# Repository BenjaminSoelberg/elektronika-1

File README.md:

# ELEKTRONIKA-1 - A replacement module for a USSR made vintage LED watch anno 1978

## It actually works
The watch works very well and I am very happy with it.

It has been my daily driver for a few months by now with no problems what so ever.

It can show time, date and year which was more or less what you got in the original.

The module is based around:
* Texas Instruments MSP430fr2433 micro controller
* Austria Micro Systems AS1115 64 bit LED driver
* Vintage Hewlett Packard HP-5082-7414 4x7 segments + dot display
* CR2032 battery

## Source code
Modules:

* buttons.c - This is the button driver and it handles button events 
* clocksystem.c - Initializes the clock system in the MSP430
* config.h - Global timing and clock constants
* debounce.c - The button debounce detection and filtering using a sliding bit buffer
* display.c - Display update functions like content and intensity.
* driverlib_ng.c - My overloading of the TI MSP430 driver lib for better pin handling
* elektronika.c - Handles the control flow of everything
* render.c - Simple 7 segment 'font' driver
* rtcclock.c - Realtime clock module supporting adjusting date and time
* utils.h - Macros for entering and exiting critical sections

Written using Code Composer Studio.

## Hardware

The PCB is designed in KiCad and is my first ever multi layer PCB.

Button contacts are made with what would normally be plated half castellated holes but they are in reality nothing more than partially routed mounting holes.

The AS1115 display driver was choosen as it is able to drive the LED display directly as well as adjusting the current.

A lot of care has been taken to save as much power as possible.  Battery life is messured to be around 10 years (less if you actually press buttons as the LED technology from the late 1970 uses a lot of current).

The watch uses around 0.002 mA/h in standby and 10-40 mA/h while the display is on.

Originally the two 1.55 V batteries didn't even last a year.

Schematics:

The four PCB layers:

3D render of front PCB:

3D render of back PCB:

What the original module looks like:

New watch module:

New watch module installed:

Showing time:

Showning date:

On wrist:

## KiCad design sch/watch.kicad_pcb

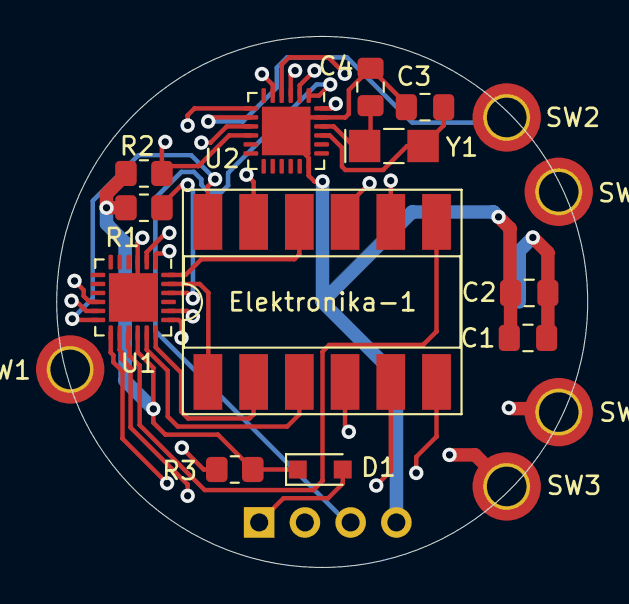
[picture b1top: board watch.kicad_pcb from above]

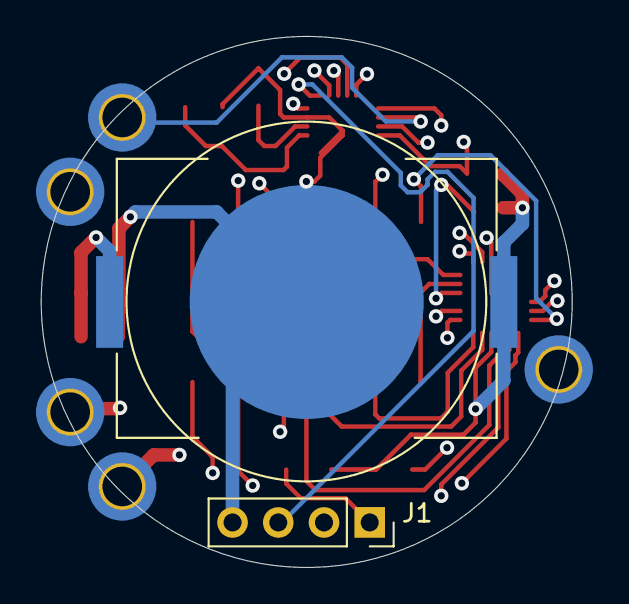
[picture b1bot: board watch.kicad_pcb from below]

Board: 4 copper layers, 29.5 x 29.5 mm, 19 parts (2 on the bottom side), 27 nets.

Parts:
BT1: 3V CR2032; BAT-HLD-001
C1: 10uF*; C_0805_2012Metric_Pad1.18x1.45mm_HandSolder
C2: 12pF*; C_0805_2012Metric_Pad1.18x1.45mm_HandSolder
C3, C4: 12pF; C_0805_2012Metric_Pad1.18x1.45mm_HandSolder
D1: 1N4148; D_SOD-323_HandSoldering
Elektronika-1: HP-5082-7414; DIP-12_W8.89mm_SMDSocket_LongPads
J1: eZ-FET; PinSocket_1x04_P2.54mm_Vertical
R1, R2: 10k; R_0805_2012Metric_Pad1.20x1.40mm_HandSolder
R3: 40k; R_0805_2012Metric_Pad1.20x1.40mm_HandSolder
SW1: SW1; MountingHole_2.2mm_M2_DIN965_Pad_TopBottom
SW2: SW2; MountingHole_2.2mm_M2_DIN965_Pad_TopBottom
SW3: SW3; MountingHole_2.2mm_M2_DIN965_Pad_TopBottom
SW4: SW4; MountingHole_2.2mm_M2_DIN965_Pad_TopBottom
SW5: SW5; MountingHole_2.2mm_M2_DIN965_Pad_TopBottom
U1: AS1115; QFN-24-1EP_4x4mm_P0.5mm_EP2.7x2.7mm
U2: MSP430FR2433; QFN-24-1EP_4x4mm_P0.5mm_EP2.7x2.7mm
Y1: 32768Hz; Crystal_SMD_MicroCrystal_CC7V-T1A-2Pin_3.2x1.5mm_HandSolder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

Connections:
+3V0: BT1.P1, BT1.P2, C1.1, C2.1, D1.1, R1.1, R2.1, R3.1, U1.16, U2.24
GND: BT1.N1, C1.2, C2.2, C3.2, C4.2, J1.4, U1.3, U1.25, U2.18, U2.23, U2.25
I2C_SDA: R1.2, U1.22, U2.9
I2C_SLC: R2.2, U1.11, U2.10
unnamed: C3.1, U2.21, Y1.2
unnamed: C4.1, U2.22, Y1.1
unnamed: D1.2, J1.1
unnamed: Elektronika-1.1, U1.23
unnamed: Elektronika-1.2, U1.18
unnamed: Elektronika-1.3, U1.17
unnamed: Elektronika-1.4, U1.1
unnamed: Elektronika-1.5, U1.19
unnamed: Elektronika-1.6, U1.2
unnamed: Elektronika-1.7, U1.15
unnamed: Elektronika-1.8, U1.20
unnamed: Elektronika-1.9, U1.13
unnamed: Elektronika-1.10, U1.24
unnamed: Elektronika-1.11, U1.14
unnamed: Elektronika-1.12, U1.12
unnamed: R3.2, U1.10
unnamed: SW1.1, U2.7
unnamed: SW2.1, U2.8
unnamed: SW3.1, U2.3
unnamed: SW4.1, U2.4
unnamed: SW5.1, U2.5
RST_SBWTDIO: J1.3, U2.1
TST_SBWTCK: J1.2, U2.2

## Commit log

2021-05-05 ccs file removed
2021-05-13 added a wip button driver, display drivet etc
2021-05-13 added an 'ignore' folder to .gitignore
2021-05-13 working on button driver
2021-05-14 Added an empty button driver, and a initial display driver, all still untested
2021-05-19 Fixed a very annoying bug where writing to port one overwrote port two. The bug were caused by copy and pasting code from original driverlib. Took way to long to find...
    removed the blink test code from buttons and rtc as well as moved to ext 32khz crystal as osc
    added a WIP version of the schematics as well as moved stuff around. Also added some datasheet PDFs
2021-05-23 Added a new clocksystem module following the same format as other modules like the display and button driver. Updated the display driver to use AS1115 i2c driver chip to move multiplexing away from t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
2021-05-25 added some docs plus sort and rename
2021-06-02 Added a new button system
2021-06-05 Changed minimal button press response time to 100ms.\nFixed bug button driver
2021-06-10 Added a (simple) button repeating handler. Added debug config options, button handling and display as well as i2c dummy stubs. Added setting of time and date handlinging
2021-06-17 updated schematic and pcb as well as component libs
2021-06-27 Updated the PCB
2021-06-27 initial version
2021-06-27 Added schematics
2021-06-28 Added production files that was uploaded to JLCPCB.com
2021-06-29 added JLCPCB production files
2021-08-29 Fixed a bad and untested i2c configuration now that I actually have a real AS1115 chip to test with
2021-08-29 Code cleanup
2021-08-30 font fix for digits 2 and 3
2021-08-30 Fixed missing digit and added a 'show mmss' debug loop
2021-08-31 Fixed old display content shown for a brief time upon Display_start call
2021-09-06 Create LICENSE
2021-09-09 Added startup display animation Fixed button pins from pullup to pulldown (The watch case will be connected to the positive battery terminal) Fixed button interrupt from port2 (which it is on the lau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
2021-09-09 Updated the README.md as the watch module now has passed initial verification test
2021-09-09 Added intensity adjustment via the SET_H and SET_L buttons
2021-09-10 Added USSr EL-1 startup text
2021-09-11 Added a simple i2c timeout detection with automatic reboot Added a blinking dot while showing time
2022-03-29 Added real life pictures
2022-03-29 Title change to reflect the heritage
2022-03-29 updated readme with more sw and hw info
2022-03-29 reordering of pictures
